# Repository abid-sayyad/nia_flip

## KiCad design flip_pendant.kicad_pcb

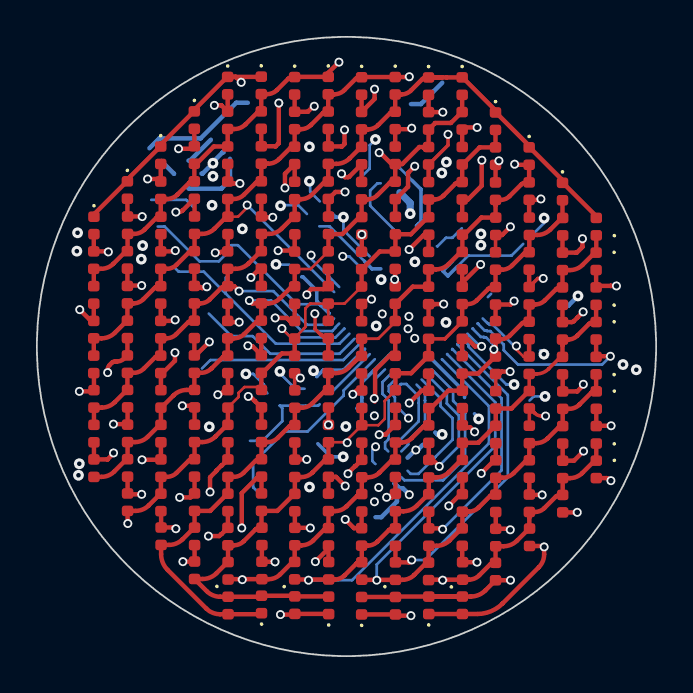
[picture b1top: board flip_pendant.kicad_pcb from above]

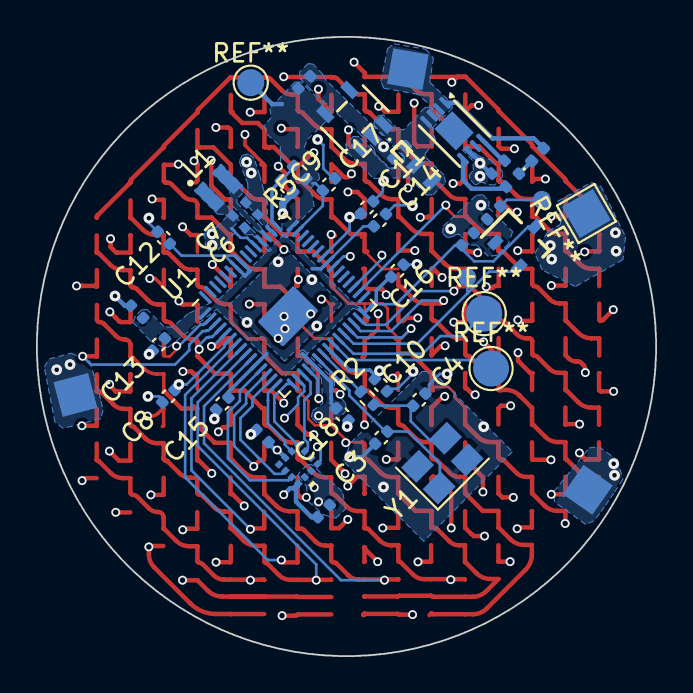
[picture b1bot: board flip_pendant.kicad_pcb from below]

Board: 4 copper layers, 34.4 x 34.4 mm, 251 parts (35 on the bottom side), 36 nets.

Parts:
C1, C2: 1uF; C_0402_1005Metric
C3, C4: 15p; C_0402_1005Metric
C3#2: 0.1uF; C_0402_1005Metric
C6, C7: 100nF; C_0402_1005Metric
C6#2, C7#2: 4.7u; C_0402_1005Metric_small_pads
C8, C11, C12, C13, C14, C15, C16, C17, C18: 100n; C_0402_1005Metric
C9, C10: 4.7u; C_0402_1005Metric
C19: 10u; C_0402_1005Metric
D1, D2, D3, D4, D5, D6, D7, D8, D9, D10, D11, D12, D13, D14, D15, D16, D17, D18, D19, D20, D21, D22, D23, D24, D25, D26, D27, D28, D29, D30, D31, D32, D33, D34, D35, D36, D37, D38, D39, D40, D41, D42, D43, D44, D45, D46, D47, D48, D49, D50, D51, D52, D53, D54, D55, D56, D57, D58, D59, D60, D61, D62, D63, D64, D65, D66, D67, D68, D69, D70, D71, D72, D73, D74, D75, D76, D77, D78, D79, D80, D81, D82, D83, D84, D85, D86, D87, D88, D89, D90, D91, D92, D93, D94, D95, D96, D97, D98, D99, D100, D101, D102, D103, D104, D105, D106, D107, D108, D109, D110, D111, D112, D113, D114, D115, D116, D117, D118, D119, D120, D121, D122, D123, D124, D125, D126, D127, D128, D129, D130, D131, D132, D133, D134, D135, D136, D137, D138, D139, D140, D141, D142, D143, D144, D145, D146, D147, D148, D149, D150, D151, D152, D153, D154, D155, D156, D157, D158, D159, D160, D161, D162, D163, D164, D165, D166, D167, D168, D169, D170, D171, D172, D173, D174, D175, D176, D177, D178, D179, D180, D181, D182, D183, D184, D185, D186, D187, D188, D189, D190, D191, D192, D193, D194, D195, D196, D197, D198, D199, D200, D201, D202, D203, D204, D205, D206, D207, D208, D209, D210, D211, D212, D213, D214, D215, D216, D241: LED_Small; LED_0402_1005Metric
H1: 1565322-1; 15653221
L1: 3.3u; L_pol_2016
R1: 470; R_0402_1005Metric
R2, R4: 1k; R_0402_1005Metric
R3: 2K; R_0402_1005Metric
R5: 33; R_0402_1005Metric
U1: TPS3839A09DQNR; DBZ0003A_L
U1#2: RP2350_60QFN; RP2350-QFN-60-1EP_7x7_P0.4mm_EP3.4x3.4mm_ThermalVias
U2: TPS7A0215PDQNR; SOT23_DBV_TEX
U3: MCP73832-2-MC; DFN-8-1EP_3x2mm_P0.5mm_EP1.7x1.4mm
U5: BMA400; QFN_BMA400_BOS-M
Y1: ABM8-272-T3; Crystal_SMD_3225-4Pin_3.2x2.5mm

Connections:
+1V1: C7#2.1, C8.1, C10.1, C11.1, L1.1, U1#2.6 (DVDD), U1#2.23 (DVDD), U1#2.39 (DVDD), U1#2.50 (VREG_FB)
+3V3: C1.1, C3#2.2, C6.2, C6#2.1, C7.1, C12.1, C13.1, C14.1, C15.1, C16.1, C17.1, C18.1, C19.1, R5.1, U1.3 (VDD), U1#2.1 (IOVDD), U1#2.11 (IOVDD), U1#2.20 (IOVDD), U1#2.30 (IOVDD), U1#2.38 (IOVDD), U1#2.44 (ADC_AVDD), U1#2.45 (IOVDD), U1#2.49 (VREG_VIN), U1#2.53 (USB_OTP_VDD), U1#2.54 (QSPI_IOVDD), U2.5 (OUT), U5.3 (VDDIO), U5.7 (VDD)
+3V8: C2.2, H1.1, H1.2, U2.1 (IN), U2.3 (EN), U3.3 (V_{BAT}), U3.4 (V_{BAT})
/GPIO11: U1#2.15 (GPIO11), U5.2 (SDX)
/GPIO12: U1#2.16 (GPIO12), U5.1 (SDO)
/GPIO14: U1#2.18 (GPIO14), U5.12 (SCX)
/RUN: U1.2 (RESET_N), U1#2.26 (RUN)
/VREG_AVDD: C9.1, R5.2, U1#2.46 (VREG_AVDD)
/VREG_LX: L1.2, U1#2.48 (VREG_LX)
/XIN: C3.1, U1#2.21 (XIN), Y1.1
/XOUT: R2.1, U1#2.22 (XOUT)
CS: U1#2.17 (GPIO13), U5.10 (CSB)
GND: C1.2, C2.1, C3.2, C3#2.1, C4.2, C6.1, C6#2.2, C7.2, C7#2.2, C8.2, C9.2, C10.2, C11.2, C12.2, C13.2, C14.2, C15.2, C16.2, C17.2, C18.2, C19.2, R3.2, R4.2, U1.1 (GND), U1#2.47 (VREG_PGND), U1#2.61 (GND), U2.2 (GND), U3.6 (V_{SS}), U5.8 (GNDIO), U5.9 (GND), Y1.2, Y1.4
GPIO1: D9.2 (A), D20.1 (K), D21.2 (A), D34.1 (K), D35.2 (A), D50.1 (K), D51.2 (A), D67.1 (K), D68.2 (A), D84.1 (K), D85.2 (A), D101.1 (K), D102.2 (A), D118.1 (K), D119.2 (A), D135.1 (K), D136.2 (A), D152.1 (K), D153.2 (A), D169.1 (K), D170.2 (A), D185.1 (K), D186.2 (A), D201.1 (K), D202.2 (A), U1#2.19 (GPIO15)
GPIO2: D19.2 (A), D32.1 (K), D33.2 (A), D48.1 (K), D49.2 (A), D65.1 (K), D66.2 (A), D82.1 (K), D83.2 (A), D99.1 (K), D100.2 (A), D116.1 (K), D117.2 (A), D133.1 (K), D134.2 (A), D150.1 (K), D151.2 (A), D167.1 (K), D168.2 (A), D183.1 (K), D184.2 (A), D199.1 (K), D200.2 (A), D215.1 (K), D216.2 (A), U1#2.13 (GPIO9)
GPIO3: D1.2 (A), D10.1 (K), D11.2 (A), D22.1 (K), D23.2 (A), D36.1 (K), D37.2 (A), D52.1 (K), D53.2 (A), D69.1 (K), D70.2 (A), D86.1 (K), D87.2 (A), D103.1 (K), D104.2 (A), D120.1 (K), D121.2 (A), D137.1 (K), D138.2 (A), D154.1 (K), D155.2 (A), D171.1 (K), D172.2 (A), U1#2.5 (GPIO3)
GPIO4: D31.2 (A), D46.1 (K), D47.2 (A), D63.1 (K), D64.2 (A), D80.1 (K), D81.2 (A), D97.1 (K), D98.2 (A), D114.1 (K), D115.2 (A), D131.1 (K), D132.2 (A), D148.1 (K), D149.2 (A), D165.1 (K), D166.2 (A), D181.1 (K), D182.2 (A), D197.1 (K), D198.2 (A), D201.2 (A), D202.1 (K), D213.1 (K), D214.2 (A), D215.2 (A), D216.1 (K), U1#2.8 (GPIO5)
GPIO5: D1.1 (K), D2.1 (K), D3.2 (A), D9.1 (K), D12.1 (K), D13.2 (A), D19.1 (K), D24.1 (K), D25.2 (A), D31.1 (K), D38.1 (K), D39.2 (A), D45.1 (K), D54.1 (K), D55.2 (A), D71.1 (K), D72.2 (A), D88.1 (K), D89.2 (A), D105.1 (K), D106.2 (A), D122.1 (K), D123.2 (A), D139.1 (K), D140.2 (A), D156.2 (A), U1#2.2 (GPIO0)
GPIO6: D45.2 (A), D61.1 (K), D62.2 (A), D78.1 (K), D79.2 (A), D95.1 (K), D96.2 (A), D112.1 (K), D113.2 (A), D129.1 (K), D130.2 (A), D146.1 (K), D147.2 (A), D156.1 (K), D163.1 (K), D164.2 (A), D171.2 (A), D172.1 (K), D179.1 (K), D180.2 (A), D185.2 (A), D186.1 (K), D195.1 (K), D196.2 (A), D199.2 (A), D200.1 (K), D211.1 (K), D212.2 (A), D213.2 (A), D214.1 (K), U1#2.7 (GPIO4)
GPIO7: D2.2 (A), D3.1 (K), D4.1 (K), D5.2 (A), D10.2 (A), D11.1 (K), D14.1 (K), D15.2 (A), D20.2 (A), D21.1 (K), D26.1 (K), D27.2 (A), D32.2 (A), D33.1 (K), D40.1 (K), D41.2 (A), D46.2 (A), D47.1 (K), D56.1 (K), D57.2 (A), D61.2 (A), D62.1 (K), D73.1 (K), D74.2 (A), D77.1 (K), D90.1 (K), D91.2 (A), D107.1 (K), D108.2 (A), D124.2 (A), U1#2.3 (GPIO1)
GPIO8: D77.2 (A), D93.1 (K), D94.2 (A), D110.1 (K), D111.2 (A), D124.1 (K), D127.1 (K), D128.2 (A), D139.2 (A), D140.1 (K), D144.1 (K), D145.2 (A), D154.2 (A), D155.1 (K), D161.1 (K), D162.2 (A), D169.2 (A), D170.1 (K), D177.1 (K), D178.2 (A), D183.2 (A), D184.1 (K), D193.1 (K), D194.2 (A), D197.2 (A), D198.1 (K), D209.1 (K), D210.2 (A), D211.2 (A), D212.1 (K), U1#2.9 (GPIO6)
GPIO9: D4.2 (A), D5.1 (K), D6.1 (K), D7.2 (A), D12.2 (A), D13.1 (K), D16.1 (K), D17.2 (A), D22.2 (A), D23.1 (K), D28.1 (K), D29.2 (A), D34.2 (A), D35.1 (K), D42.1 (K), D43.2 (A), D48.2 (A), D49.1 (K), D58.1 (K), D59.2 (A), D63.2 (A), D64.1 (K), D75.1 (K), D76.2 (A), D78.2 (A), D79.1 (K), D92.2 (A), D93.2 (A), D94.1 (K), D109.1 (K), U1#2.32 (GPIO20)
GPIO10: D92.1 (K), D107.2 (A), D108.1 (K), D109.2 (A), D122.2 (A), D123.1 (K), D125.1 (K), D126.2 (A), D137.2 (A), D138.1 (K), D142.1 (K), D143.2 (A), D152.2 (A), D153.1 (K), D159.1 (K), D160.2 (A), D167.2 (A), D168.1 (K), D175.1 (K), D176.2 (A), D181.2 (A), D182.1 (K), D191.1 (K), D192.2 (A), D195.2 (A), D196.1 (K), D207.1 (K), D208.2 (A), D209.2 (A), D210.1 (K), U1#2.10 (GPIO7)
GPIO15: D6.2 (A), D7.1 (K), D8.1 (K), D14.2 (A), D15.1 (K), D18.1 (K), D24.2 (A), D25.1 (K), D30.1 (K), D36.2 (A), D37.1 (K), D44.1 (K), D50.2 (A), D51.1 (K), D60.2 (A), D65.2 (A), D66.1 (K), D80.2 (A), D81.1 (K), D95.2 (A), D96.1 (K), D110.2 (A), D111.1 (K), D125.2 (A), D126.1 (K), D141.1 (K), U1#2.29 (GPIO18)
GPIO16: D60.1 (K), D75.2 (A), D76.1 (K), D90.2 (A), D91.1 (K), D105.2 (A), D106.1 (K), D120.2 (A), D121.1 (K), D135.2 (A), D136.1 (K), D141.2 (A), D150.2 (A), D151.1 (K), D157.1 (K), D158.2 (A), D165.2 (A), D166.1 (K), D173.1 (K), D174.2 (A), D179.2 (A), D180.1 (K), D189.1 (K), D190.2 (A), D193.2 (A), D194.1 (K), D205.1 (K), D206.2 (A), D207.2 (A), D208.1 (K), U1#2.4 (GPIO2)
GPIO17: D8.2 (A), D16.2 (A), D17.1 (K), D26.2 (A), D27.1 (K), D38.2 (A), D39.1 (K), D52.2 (A), D53.1 (K), D67.2 (A), D68.1 (K), D82.2 (A), D83.1 (K), D97.2 (A), D98.1 (K), D112.2 (A), D113.1 (K), D127.2 (A), D128.1 (K), D142.2 (A), D143.1 (K), D157.2 (A), D158.1 (K), U1#2.28 (GPIO17)
GPIO18: D44.2 (A), D58.2 (A), D59.1 (K), D73.2 (A), D74.1 (K), D88.2 (A), D89.1 (K), D103.2 (A), D104.1 (K), D118.2 (A), D119.1 (K), D133.2 (A), D134.1 (K), D148.2 (A), D149.1 (K), D163.2 (A), D164.1 (K), D177.2 (A), D178.1 (K), D187.1 (K), D188.2 (A), D191.2 (A), D192.1 (K), D203.1 (K), D204.2 (A), D205.2 (A), D206.1 (K), U1#2.37 (GPIO25)
GPIO19: D18.2 (A), D28.2 (A), D29.1 (K), D40.2 (A), D41.1 (K), D54.2 (A), D55.1 (K), D69.2 (A), D70.1 (K), D84.2 (A), D85.1 (K), D99.2 (A), D100.1 (K), D114.2 (A), D115.1 (K), D129.2 (A), D130.1 (K), D144.2 (A), D145.1 (K), D159.2 (A), D160.1 (K), D173.2 (A), D174.1 (K), D187.2 (A), D188.1 (K), U1#2.27 (GPIO16)
GPIO20: D30.2 (A), D42.2 (A), D43.1 (K), D56.2 (A), D57.1 (K), D71.2 (A), D72.1 (K), D86.2 (A), D87.1 (K), D101.2 (A), D102.1 (K), D116.2 (A), D117.1 (K), D131.2 (A), D132.1 (K), D146.2 (A), D147.1 (K), D161.2 (A), D162.1 (K), D175.2 (A), D176.1 (K), D189.2 (A), D190.1 (K), D203.2 (A), D204.1 (K), U1#2.33 (GPIO21)
INT1: U1#2.14 (GPIO10), U5.5 (INT1)
INT2: U1#2.12 (GPIO8), U5.6 (INT2)
unnamed: C4.1, R2.2, Y1.3
unnamed: D241.1 (K), R1.1
unnamed: R3.1, U3.8 (PROG)
unnamed: R1.2, U3.5 (STAT)
VIN: D241.2 (A), U3.1 (V_{DD}), U3.2 (V_{DD})

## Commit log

2026-05-04 nia_v2
2026-05-05 clean up in2.cu
